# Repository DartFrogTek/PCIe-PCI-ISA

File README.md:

# Potential PCIe to PCI to ISA BUS pathway.

IT FREAKING WORKS ~~~ ISA DDMA ON WIN 10 ~~~ PCM AUDIO PLAYING ON A REAL ISA PICOGUS ON WIN10 !!!

A REAL WORLD FIRST!!! See https://www.vogons.org/viewtopic.php?t=111221 for more details.

---

This repository contains information and files on how to potentially provide modern systems with an ISA bus including ISA DMA.

More even more historical dev information that's available on the "dISAppointment - LPC to ISA adapter - ISA on modern motherboard" thread.
https://www.vogons.org/viewtopic.php?t=93291

## IT8888 based ISA8888 PCI to ISA Card
- This card/breakout board should allow a user-provided ISA Card to be translated into a PCI card via IT8888.
- ISA DMA is facilitated by PCI bus mastering through the IT8888 chip.
- Project is in KiCAD format.
- *WIP*

## ACPI SSDT 
- A way to configure motherboard bus bridges to allow I/O forwarding.
- *Boilerplate implementation*, given to me by an absolute legend.
- Added steps on how to find bridge and modify `IT8893_ACPI_SSDT.asl` for compiling.
- `IT8893_ACPI_SSDT.asl` Compiles *UNTESTED - DO NOT USE*

## DXE Driver
- Last resort, given to me by an absolute legend.
- *Boilerplate implementation*

## GRUB
- It's possible to configure PCI bridges using GRUB, avoiding the need for DXE Drivers or ACPI SSDT. 
- Requires GRUB and potentially turning off secure boot. 

## CHIPSEC
- Various LPC DMA tests with CHIPSEC
- Scripts get placed in 'chipsec-1.13.11\chipsec\modules\common'
- Tests are ran with:
  - "python chipsec_main.py -m common.lpc_dma_check"
  - "python chipsec_main.py -m common.lpc_dma_z390_test"
  - "python chipsec_main.py -m common.lpc_dma_h81_z390_test"
- *Tests work, but might crash your system.*

## Extras
- Datasheets, Documents, Pin Mappings.

## Thanks
- Everyone at Vogons, seriously thanks.
- Absolute Legend #1, #2, and #3. [Names redacted to protect their jobs]
- My wife.

Without my wife, everyone at Vogons, and the legends, none of this would likely exist.

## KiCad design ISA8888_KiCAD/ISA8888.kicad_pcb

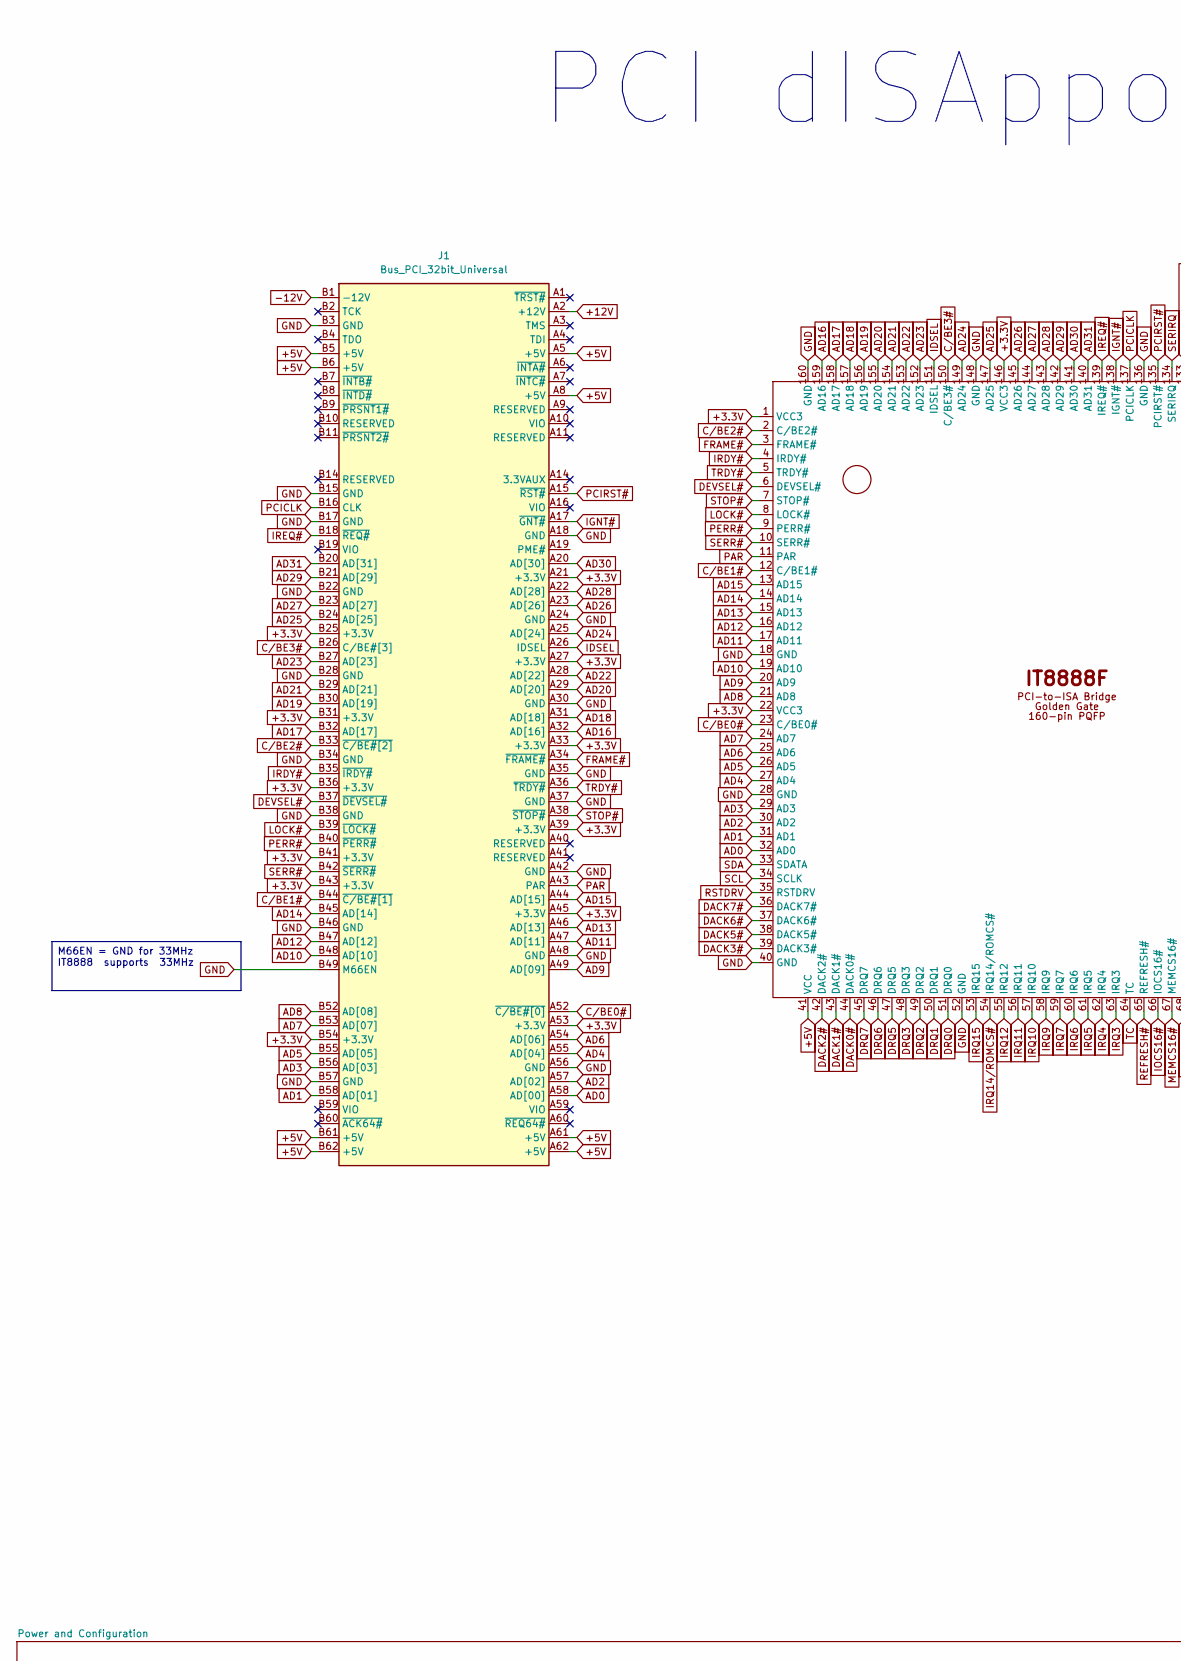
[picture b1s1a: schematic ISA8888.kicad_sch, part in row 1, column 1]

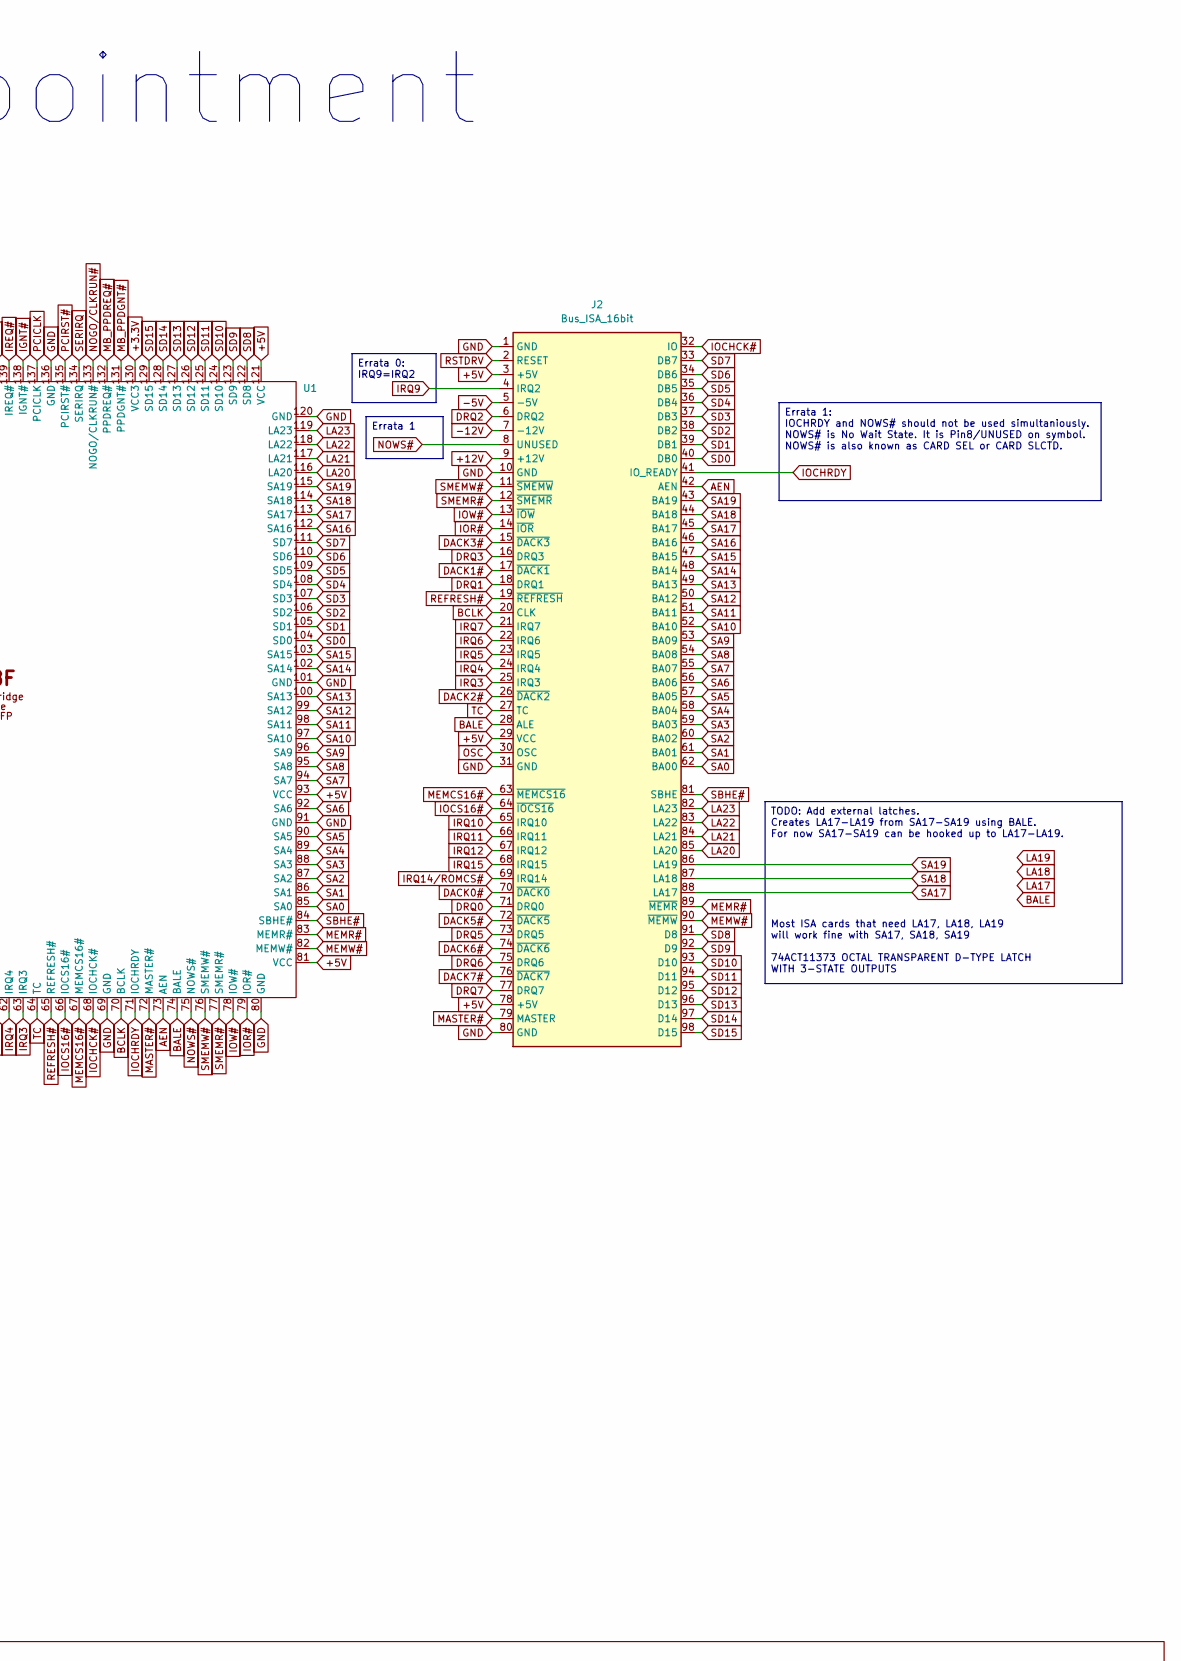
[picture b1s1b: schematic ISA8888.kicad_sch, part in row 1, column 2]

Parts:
J1: Bus_PCI_32bit_Universal; BUS_PCI
J2: Bus_ISA_16bit; CONN_EBC49_SUL_Fixed
U1: PQFP-160_28x28mm_P0.65mm

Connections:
+3.3V: J1.A21 (+3.3V), J1.A27 (+3.3V), J1.A33 (+3.3V), J1.A39 (+3.3V), J1.A45 (+3.3V), J1.A53 (+3.3V), J1.B25 (+3.3V), J1.B31 (+3.3V), J1.B36 (+3.3V), J1.B41 (+3.3V), J1.B43 (+3.3V), J1.B54 (+3.3V), U1.1 (VCC3), U1.22 (VCC3), U1.130 (VCC3), U1.146 (VCC3); also elsewhere on the board
+5V: J1.A5 (+5V), J1.A8 (+5V), J1.A61 (+5V), J1.A62 (+5V), J1.B5 (+5V), J1.B6 (+5V), J1.B61 (+5V), J1.B62 (+5V), J2.3 (+5V), J2.29 (VCC), J2.78 (+5V), U1.41 (VCC), U1.81 (VCC), U1.93 (VCC), U1.121 (VCC); also elsewhere on the board
+12V: J1.A2 (+12V), J2.9 (+12V); also elsewhere on the board
-5V: J2.5 (-5V); also elsewhere on the board
-12V: J1.B1 (-12V), J2.7 (-12V); also elsewhere on the board
AD0: J1.A58 (AD[00]), U1.32 (AD0)
AD1: J1.B58 (AD[01]), U1.31 (AD1)
AD2: J1.A57 (AD[02]), U1.30 (AD2)
AD3: J1.B56 (AD[03]), U1.29 (AD3)
AD4: J1.A55 (AD[04]), U1.27 (AD4)
AD5: J1.B55 (AD[05]), U1.26 (AD5)
AD6: J1.A54 (AD[06]), U1.25 (AD6)
AD7: J1.B53 (AD[07]), U1.24 (AD7)
AD8: J1.B52 (AD[08]), U1.21 (AD8)
AD9: J1.A49 (AD[09]), U1.20 (AD9)
AD10: J1.B48 (AD[10]), U1.19 (AD10)
AD11: J1.A47 (AD[11]), U1.17 (AD11)
AD12: J1.B47 (AD[12]), U1.16 (AD12)
AD13: J1.A46 (AD[13]), U1.15 (AD13)
AD14: J1.B45 (AD[14]), U1.14 (AD14)
AD15: J1.A44 (AD[15]), U1.13 (AD15)
AD16: J1.A32 (AD[16]), U1.159 (AD16)
AD17: J1.B32 (AD[17]), U1.158 (AD17)
AD18: J1.A31 (AD[18]), U1.157 (AD18)
AD19: J1.B30 (AD[19]), U1.156 (AD19)
AD20: J1.A29 (AD[20]), U1.155 (AD20)
AD21: J1.B29 (AD[21]), U1.154 (AD21)
AD22: J1.A28 (AD[22]), U1.153 (AD22)
AD23: J1.B27 (AD[23]), U1.152 (AD23)
AD24: J1.A25 (AD[24]), U1.149 (AD24)
AD25: J1.B24 (AD[25]), U1.147 (AD25)
AD26: J1.A23 (AD[26]), U1.145 (AD26)
AD27: J1.B23 (AD[27]), U1.144 (AD27)
AD28: J1.A22 (AD[28]), U1.143 (AD28)
AD29: J1.B21 (AD[29]), U1.142 (AD29)
AD30: J1.A20 (AD[30]), U1.141 (AD30)
AD31: J1.B20 (AD[31]), U1.140 (AD31)
AEN: J2.42 (AEN), U1.73 (AEN); also elsewhere on the board
BALE: J2.28 (ALE), U1.74 (BALE); also elsewhere on the board
BCLK: J2.20 (CLK), U1.70 (BCLK)
C/BE0#: J1.A52 (~C/BE#[0]), U1.23 (C/BE0#)
C/BE1#: J1.B44 (~C/BE#[1]), U1.12 (C/BE1#)
C/BE2#: J1.B33 (~C/BE#[2]), U1.2 (C/BE2#)
C/BE3#: J1.B26 (C/BE#[3]), U1.150 (C/BE3#)
DACK0#: J2.70 (~DACK0), U1.44 (DACK0#)
DACK1#: J2.17 (~DACK1), U1.43 (DACK1#)
DACK2#: J2.26 (~DACK2), U1.42 (DACK2#)
DACK3#: J2.15 (~DACK3), U1.39 (DACK3#)
DACK5#: J2.72 (~DACK5), U1.38 (DACK5#)
DACK6#: J2.74 (~DACK6), U1.37 (DACK6#)
DACK7#: J2.76 (~DACK7), U1.36 (DACK7#)
DEVSEL#: J1.B37 (~DEVSEL#), U1.6 (DEVSEL#)
DRQ0: J2.71 (DRQ0), U1.51 (DRQ0); also elsewhere on the board
DRQ1: J2.18 (DRQ1), U1.50 (DRQ1); also elsewhere on the board
DRQ2: J2.6 (DRQ2), U1.49 (DRQ2); also elsewhere on the board
DRQ3: J2.16 (DRQ3), U1.48 (DRQ3); also elsewhere on the board
DRQ5: J2.73 (DRQ5), U1.47 (DRQ5); also elsewhere on the board
DRQ6: J2.75 (DRQ6), U1.46 (DRQ6); also elsewhere on the board
DRQ7: J2.77 (DRQ7), U1.45 (DRQ7); also elsewhere on the board
FRAME#: J1.A34 (~FRAME#), U1.3 (FRAME#)
GND: J1.A18 (GND), J1.A24 (GND), J1.A30 (GND), J1.A35 (GND), J1.A37 (GND), J1.A42 (GND), J1.A48 (GND), J1.A56 (GND), J1.B3 (GND), J1.B15 (GND), J1.B17 (GND), J1.B22 (GND), J1.B28 (GND), J1.B34 (GND), J1.B38 (GND), J1.B46 (GND), J1.B49 (M66EN), J1.B57 (GND), J2.1 (GND), J2.10 (GND), J2.31 (GND), J2.80 (GND), U1.18 (GND), U1.28 (GND), U1.40 (GND), U1.52 (GND), U1.69 (GND), U1.80 (GND), U1.91 (GND), U1.101 (GND), U1.120 (GND), U1.136 (GND), U1.148 (GND), U1.160 (GND); also elsewhere on the board
IDSEL: J1.A26 (IDSEL), U1.151 (IDSEL)
IGNT#: J1.A17 (~GNT#), U1.138 (IGNT#); also elsewhere on the board
IOCHCK#: J2.32 (IO), U1.68 (IOCHCK#); also elsewhere on the board
IOCHRDY: J2.41 (IO_READY), U1.71 (IOCHRDY); also elsewhere on the board
IOCS16#: J2.64 (~IOCS16), U1.66 (IOCS16#); also elsewhere on the board
IOR#: J2.14 (~IOR), U1.79 (IOR#); also elsewhere on the board
IOW#: J2.13 (~IOW), U1.78 (IOW#); also elsewhere on the board
IRDY#: J1.B35 (~IRDY#), U1.4 (IRDY#)
IREQ#: J1.B18 (~REQ#), U1.139 (IREQ#); also elsewhere on the board
IRQ3: J2.25 (IRQ3), U1.63 (IRQ3)
IRQ4: J2.24 (IRQ4), U1.62 (IRQ4)
IRQ5: J2.23 (IRQ5), U1.61 (IRQ5)
IRQ6: J2.22 (IRQ6), U1.60 (IRQ6)
IRQ7: J2.21 (IRQ7), U1.59 (IRQ7)
IRQ9: J2.4 (IRQ2), U1.58 (IRQ9)
IRQ10: J2.65 (IRQ10), U1.57 (IRQ10)
IRQ11: J2.66 (IRQ11), U1.56 (IRQ11)
IRQ12: J2.67 (IRQ12), U1.55 (IRQ12)
IRQ14/ROMCS#: J2.69 (IRQ14), U1.54 (IRQ14/ROMCS#)
IRQ15: J2.68 (IRQ15), U1.53 (IRQ15)
LA20: J2.85 (LA20), U1.116 (LA20)
LA21: J2.84 (LA21), U1.117 (LA21)
LA22: J2.83 (LA22), U1.118 (LA22)
LA23: J2.82 (LA23), U1.119 (LA23)
LOCK#: J1.B39 (~LOCK#), U1.8 (LOCK#)
MASTER#: J2.79 (MASTER), U1.72 (MASTER#); also elsewhere on the board
MB_PPDGNT#: U1.131 (PPDGNT#); also elsewhere on the board
MB_PPDREQ#: U1.132 (PPDREQ#); also elsewhere on the board
MEMCS16#: J2.63 (~MEMCS16), U1.67 (MEMCS16#); also elsewhere on the board
MEMR#: J2.89 (~MEMR), U1.83 (MEMR#); also elsewhere on the board
MEMW#: J2.90 (~MEMW), U1.82 (MEMW#); also elsewhere on the board
NOGO/CLKRUN#: U1.133 (NOGO/CLKRUN#)
NOWS#: J2.8 (UNUSED), U1.75 (NOWS#); also elsewhere on the board
OSC: J2.30 (OSC); also elsewhere on the board
PAR: J1.A43 (PAR), U1.11 (PAR)
PCICLK: J1.B16 (CLK), U1.137 (PCICLK)
PCIRST#: J1.A15 (~RST#), U1.135 (PCIRST#)
PERR#: J1.B40 (~PERR#), U1.9 (PERR#)
REFRESH#: J2.19 (~REFRESH), U1.65 (REFRESH#); also elsewhere on the board
RSTDRV: J2.2 (RESET), U1.35 (RSTDRV)
SA0: J2.62 (BA00), U1.85 (SA0)
SA1: J2.61 (BA01), U1.86 (SA1)
SA2: J2.60 (BA02), U1.87 (SA2)
SA3: J2.59 (BA03), U1.88 (SA3)
SA4: J2.58 (BA04), U1.89 (SA4)
SA5: J2.57 (BA05), U1.90 (SA5)
SA6: J2.56 (BA06), U1.92 (SA6)
SA7: J2.55 (BA07), U1.94 (SA7)
SA8: J2.54 (BA08), U1.95 (SA8)
SA9: J2.53 (BA09), U1.96 (SA9)
SA10: J2.52 (BA10), U1.97 (SA10)
SA11: J2.51 (BA11), U1.98 (SA11)
SA12: J2.50 (BA12), U1.99 (SA12)
SA13: J2.49 (BA13), U1.100 (SA13)
SA14: J2.48 (BA14), U1.102 (SA14)
SA15: J2.47 (BA15), U1.103 (SA15)
SA16: J2.46 (BA16), U1.112 (SA16)
SA17: J2.45 (BA17), J2.88 (LA17), U1.113 (SA17)
SA18: J2.44 (BA18), J2.87 (LA18), U1.114 (SA18)
SA19: J2.43 (BA19), J2.86 (LA19), U1.115 (SA19)
SBHE#: J2.81 (SBHE), U1.84 (SBHE#)
SCL: U1.34 (SCLK); also elsewhere on the board
SD0: J2.40 (DB0), U1.104 (SD0); also elsewhere on the board
SD1: J2.39 (DB1), U1.105 (SD1); also elsewhere on the board
SD2: J2.38 (DB2), U1.106 (SD2); also elsewhere on the board
SD3: J2.37 (DB3), U1.107 (SD3); also elsewhere on the board
SD4: J2.36 (DB4), U1.108 (SD4); also elsewhere on the board
SD5: J2.35 (DB5), U1.109 (SD5); also elsewhere on the board
SD6: J2.34 (DB6), U1.110 (SD6); also elsewhere on the board
SD7: J2.33 (DB7), U1.111 (SD7); also elsewhere on the board
SD8: J2.91 (D8), U1.122 (SD8); also elsewhere on the board
SD9: J2.92 (D9), U1.123 (SD9); also elsewhere on the board
SD10: J2.93 (D10), U1.124 (SD10); also elsewhere on the board
SD11: J2.94 (D11), U1.125 (SD11); also elsewhere on the board
SD12: J2.95 (D12), U1.126 (SD12); also elsewhere on the board
SD13: J2.96 (D13), U1.127 (SD13); also elsewhere on the board
SD14: J2.97 (D14), U1.128 (SD14); also elsewhere on the board
SD15: J2.98 (D15), U1.129 (SD15); also elsewhere on the board
SDA: U1.33 (SDATA); also elsewhere on the board
SERIRQ: U1.134 (SERIRQ); also elsewhere on the board
SERR#: J1.B42 (~SERR#), U1.10 (SERR#)
SMEMR#: J2.12 (~SMEMR), U1.77 (SMEMR#); also elsewhere on the board
SMEMW#: J2.11 (~SMEMW), U1.76 (SMEMW#); also elsewhere on the board
STOP#: J1.A38 (~STOP#), U1.7 (STOP#)
TC: J2.27 (TC), U1.64 (TC); also elsewhere on the board
TRDY#: J1.A36 (~TRDY#), U1.5 (TRDY#)

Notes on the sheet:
PCI dISAppointment
Errata 1
Errata 0: IRQ9=IRQ2
Errata 1: IOCHRDY and NOWS# should not be used simultaniously. NOWS# is No Wait State. It is Pin8/UNUSED on symbol. NOWS# is also known as CARD SEL or CARD SLCTD.
TODO: Add external latches. Creates LA17-LA19 from SA17-SA19 using BALE. For now SA17-SA19 can be hooked up to LA17-LA19. Most ISA cards that need LA17, LA18, LA19 will work fine with SA17, SA18, SA19 74ACT11373 OCTAL TRANSPARENT D-TYPE LATCH WITH 3-STATE OUTPUTS
M66EN = GND for 33MHz IT8888 supports 33MHz

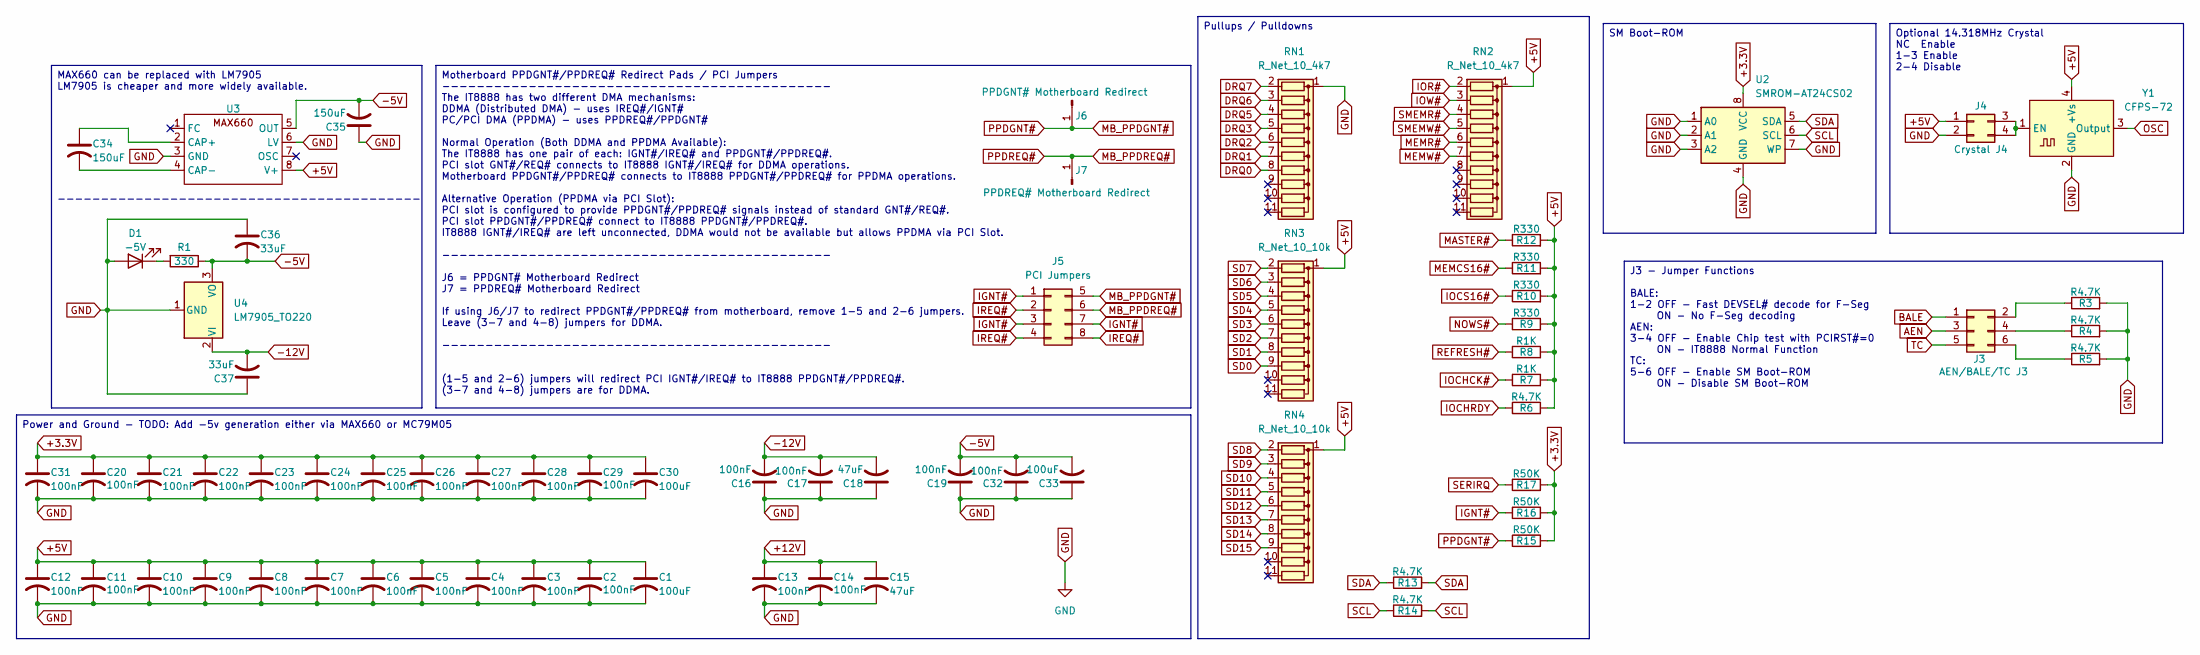
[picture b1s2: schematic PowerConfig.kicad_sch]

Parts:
C1, C30, C33: 100uF; CP_Radial_D5.0mm_P2.50mm
C2, C3, C4, C5, C6, C7, C8, C9, C10, C11, C12, C13, C14, C16, C17, C19, C20, C21, C22, C23, C24, C25, C26, C27, C28, C29, C31, C32: 100nF; C_1808_4520Metric_Pad1.72x2.30mm_HandSolder
C15, C18: 47uF; CP_Radial_D5.0mm_P2.50mm
C34, C35: 150uF; CP_Radial_D5.0mm_P2.50mm
C36, C37: 33uF; CP_Radial_D5.0mm_P2.50mm
D1: -5V; LED_D5.0mm; LCSC C99697
J3: AEN/BALE/TC J3; PinHeader_2x03_P2.00mm_Vertical
J4: Crystal J4; PinHeader_2x02_P2.00mm_Vertical
J5: PCI Jumpers; PinHeader_2x04_P2.00mm_Vertical
J6: PPDGNT# Motherboard Redirect; PinHeader_1x01_P2.00mm_Vertical
J7: PPDREQ# Motherboard Redirect; PinHeader_1x01_P2.00mm_Vertical
R1: 330; R_Axial_DIN0207_L6.3mm_D2.5mm_P7.62mm_Horizontal; LCSC C58608
R3, R4, R5, R6, R13, R14: R4.7K; R_Axial_DIN0204_L3.6mm_D1.6mm_P5.08mm_Horizontal
R7, R8: R1K; R_Axial_DIN0204_L3.6mm_D1.6mm_P5.08mm_Horizontal
R9, R10, R11, R12: R330; R_Axial_DIN0204_L3.6mm_D1.6mm_P5.08mm_Horizontal
R15, R16, R17: R50K; R_Axial_DIN0204_L3.6mm_D1.6mm_P5.08mm_Horizontal
RN1, RN2: R_Net_10_4k7; R_Array_SIP11
RN3, RN4: R_Net_10_10k; R_Array_SIP11
U2: SMROM-AT24CS02; SOIC-8_3.9x4.9mm_P1.27mm
U3: SOIC-8_3.9x4.9mm_P1.27mm
U4: LM7905_TO220; TO-220-3_Vertical
Y1: CFPS-72; Oscillator_SMD_IQD_IQXO70-4Pin_7.5x5.0mm

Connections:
+3.3V: C20.1, C21.1, C22.1, C23.1, C24.1, C25.1, C26.1, C27.1, C28.1, C29.1, C30.1, C31.1, R15.2, R16.2, R17.2, U2.8 (VCC); also elsewhere on the board
+5V: C1.1, C2.1, C3.1, C4.1, C5.1, C6.1, C7.1, C8.1, C9.1, C10.1, C11.1, C12.1, J4.1, R6.2, R7.2, R8.2, R9.2, R10.2, R11.2, R12.2, RN2.1 (common), RN3.1 (common), RN4.1 (common), U3.8 (V+), Y1.4 (+Vs); also elsewhere on the board
+12V: C13.1, C14.1, C15.1; also elsewhere on the board
-5V: C19.2, C32.2, C33.2, C35.2, C36.2, R1.1, U3.5 (OUT), U4.3 (VO); also elsewhere on the board
-12V: C16.2, C17.2, C18.2, C37.2, U4.2 (VI); also elsewhere on the board
AEN: J3.3; also elsewhere on the board
BALE: J3.1; also elsewhere on the board
DRQ0: RN1.8 (R7); also elsewhere on the board
DRQ1: RN1.7 (R6); also elsewhere on the board
DRQ2: RN1.6 (R5); also elsewhere on the board
DRQ3: RN1.5 (R4); also elsewhere on the board
DRQ5: RN1.4 (R3); also elsewhere on the board
DRQ6: RN1.3 (R2); also elsewhere on the board
DRQ7: RN1.2 (R1); also elsewhere on the board
GND: C1.2, C2.2, C3.2, C4.2, C5.2, C6.2, C7.2, C8.2, C9.2, C10.2, C11.2, C12.2, C13.2, C14.2, C15.2, C16.1, C17.1, C18.1, C19.1, C20.2, C21.2, C22.2, C23.2, C24.2, C25.2, C26.2, C27.2, C28.2, C29.2, C30.2, C31.2, C32.1, C33.1, C35.1, C36.1, C37.1, D1.2 (A), J4.2, R3.2, R4.2, R5.2, RN1.1 (common), U2.1 (A0), U2.2 (A1), U2.3 (A2), U2.4 (GND), U2.7 (WP), U3.3 (GND), U3.6 (LV), U4.1 (GND), Y1.2 (GND); also elsewhere on the board
IGNT#: J5.1, J5.3, J5.7, R16.1; also elsewhere on the board
IOCHCK#: R7.1; also elsewhere on the board
IOCHRDY: R6.1; also elsewhere on the board
IOCS16#: R10.1; also elsewhere on the board
IOR#: RN2.2 (R1); also elsewhere on the board
IOW#: RN2.3 (R2); also elsewhere on the board
IREQ#: J5.2, J5.4, J5.8; also elsewhere on the board
MASTER#: R12.1; also elsewhere on the board
MB_PPDGNT#: J5.5, J6.1, R15.1; also elsewhere on the board
MB_PPDREQ#: J5.6, J7.1; also elsewhere on the board
MEMCS16#: R11.1; also elsewhere on the board
MEMR#: RN2.6 (R5); also elsewhere on the board
MEMW#: RN2.7 (R6); also elsewhere on the board
NOWS#: R9.1; also elsewhere on the board
unnamed: D1.1 (K), R1.2
unnamed: J3.2, R3.1
unnamed: J3.4, R4.1
unnamed: J3.6, R5.1
unnamed: J4.3, J4.4, Y1.1 (EN)
unnamed: C34.1, U3.2 (CAP+)
unnamed: C34.2, U3.4 (CAP-)
OSC: Y1.3 (Output); also elsewhere on the board
REFRESH#: R8.1; also elsewhere on the board
SCL: R14.1, R14.2, U2.6 (SCL); also elsewhere on the board
SD0: RN3.9 (R8); also elsewhere on the board
SD1: RN3.8 (R7); also elsewhere on the board
SD2: RN3.7 (R6); also elsewhere on the board
SD3: RN3.6 (R5); also elsewhere on the board
SD4: RN3.5 (R4); also elsewhere on the board
SD5: RN3.4 (R3); also elsewhere on the board
SD6: RN3.3 (R2); also elsewhere on the board
SD7: RN3.2 (R1); also elsewhere on the board
SD8: RN4.2 (R1); also elsewhere on the board
SD9: RN4.3 (R2); also elsewhere on the board
SD10: RN4.4 (R3); also elsewhere on the board
SD11: RN4.5 (R4); also elsewhere on the board
SD12: RN4.6 (R5); also elsewhere on the board
SD13: RN4.7 (R6); also elsewhere on the board
SD14: RN4.8 (R7); also elsewhere on the board
SD15: RN4.9 (R8); also elsewhere on the board
SDA: R13.1, R13.2, U2.5 (SDA); also elsewhere on the board
SERIRQ: R17.1; also elsewhere on the board
SMEMR#: RN2.4 (R3); also elsewhere on the board
SMEMW#: RN2.5 (R4); also elsewhere on the board
TC: J3.5; also elsewhere on the board

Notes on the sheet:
MAX660 can be replaced with LM7905 LM7905 is cheaper and more widely available. ------------------------------------------
Motherboard PPDGNT#/PPDREQ# Redirect Pads / PCI Jumpers --------------------------------------------- The IT8888 has two different DMA mechanisms: DDMA (Distributed DMA) - uses IREQ#/IGNT# PC/PCI DMA (PPDMA) - uses PPDREQ#/PPDGNT# Normal Operation (Both DDMA and PPDMA Available): The IT8888 has one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
Pullups / Pulldowns
SM Boot-ROM
J3 - Jumper Functions BALE: 1-2 OFF - Fast DEVSEL# decode for F-Seg ON - No F-Seg decoding AEN: 3-4 OFF - Enable Chip test with PCIRST#=0 ON - IT8888 Normal Function TC: 5-6 OFF - Enable SM Boot-ROM ON - Disable SM Boot-ROM
Power and Ground - TODO: Add -5v generation either via MAX660 or MC79M05
Optional 14.318MHz Crystal NC Enable 1-3 Enable 2-4 Disable

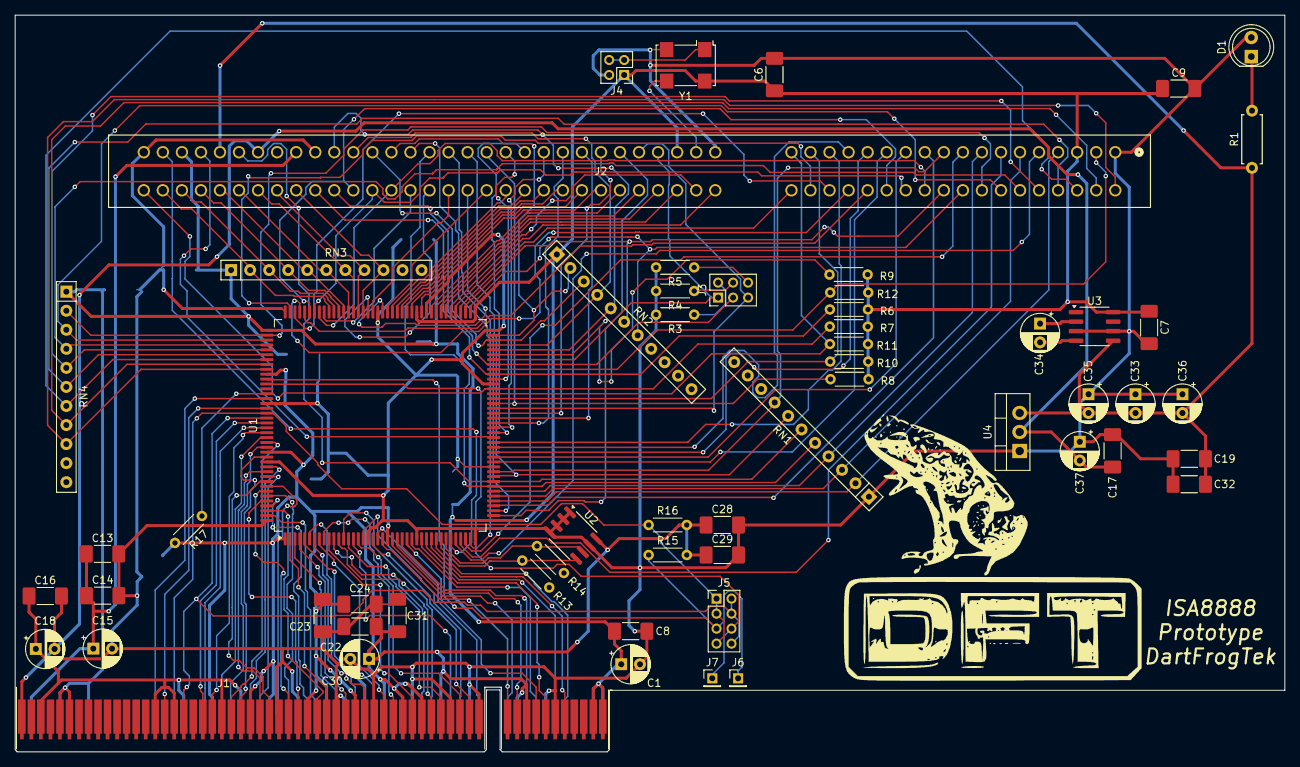
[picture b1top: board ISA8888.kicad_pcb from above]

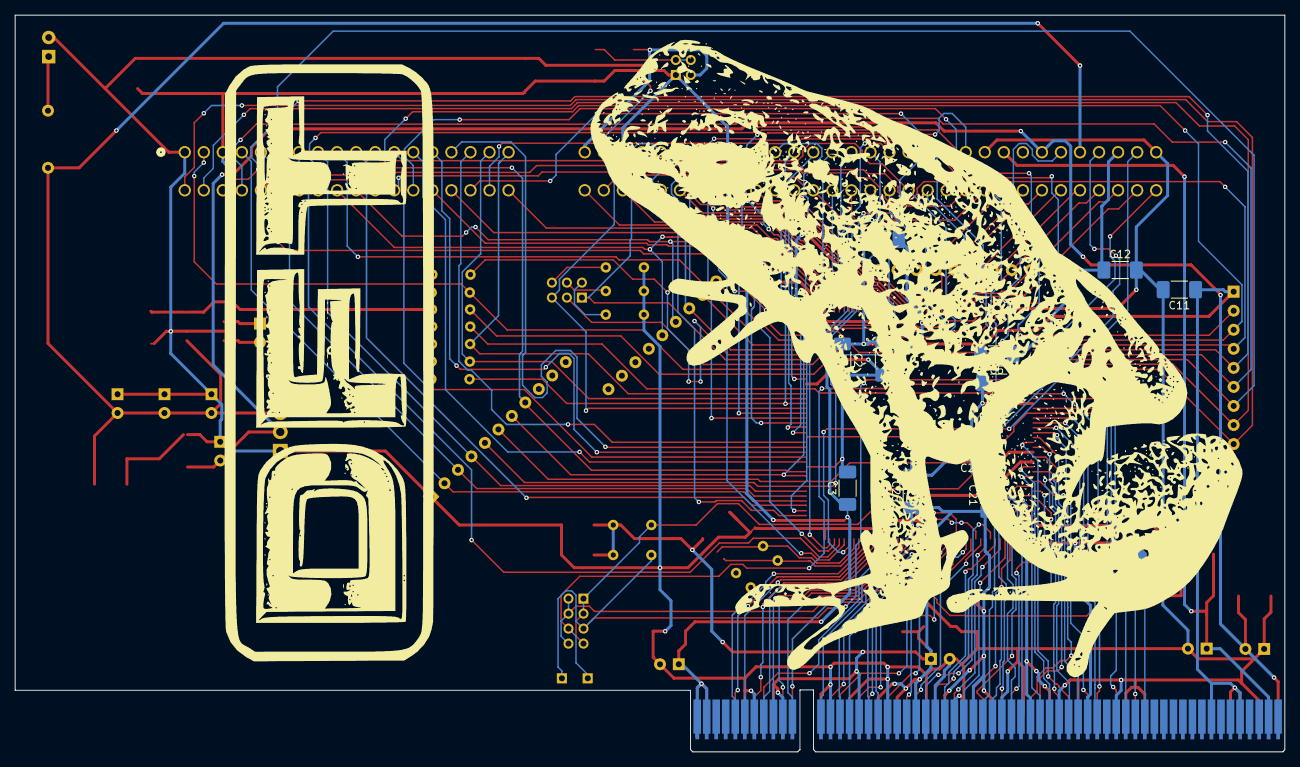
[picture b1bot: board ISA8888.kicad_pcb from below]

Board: 2 copper layers, 169.3 x 98.2 mm, 70 parts (12 on the bottom side), 153 nets.

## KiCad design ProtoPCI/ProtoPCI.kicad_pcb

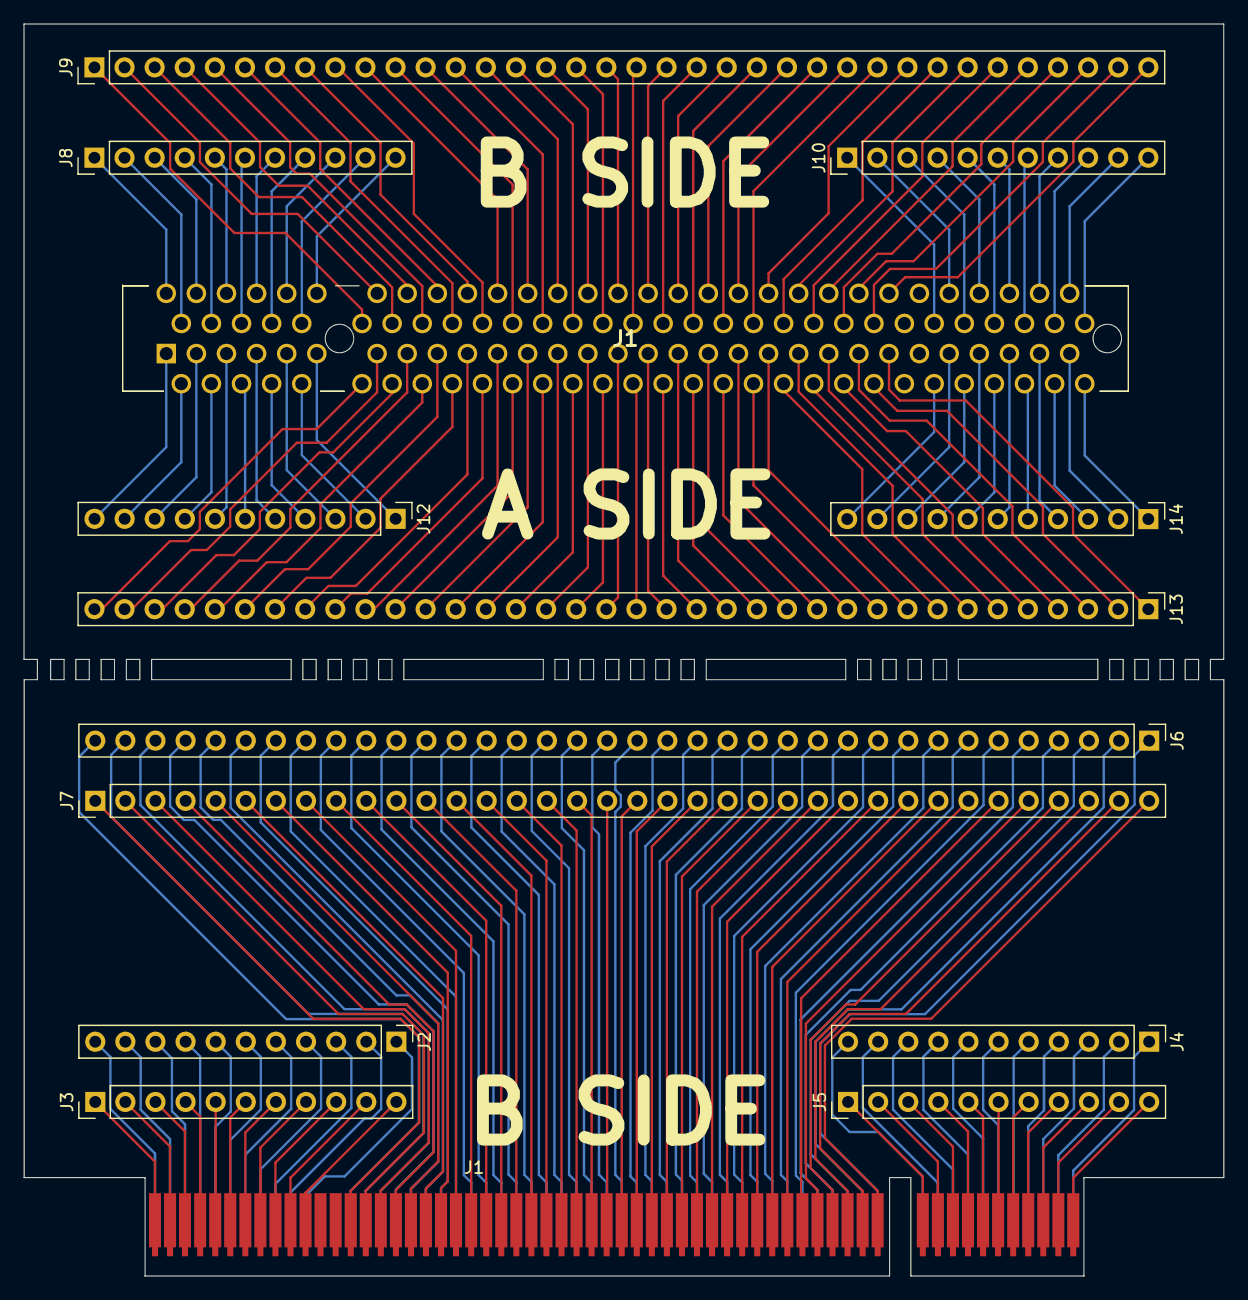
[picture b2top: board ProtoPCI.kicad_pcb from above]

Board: 2 copper layers, 101.2 x 105.6 mm, 14 parts (0 on the bottom side), 116 nets.

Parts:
J1: Bus_PCI_32bit_Universal; BUS_PCI
J1#2: Bus_PCI_32bit_Universal_Slot; 51451541
J2, J3, J4, J5, J8, J10, J12, J14: Conn_01x11_Pin; PinHeader_1x11_P2.54mm_Vertical
J6, J7, J9, J13: Conn_01x36_Pin; PinHeader_1x36_P2.54mm_Vertical

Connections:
unnamed: J1.A14 (3.3VAUX), J1#2.A14 (3.3VAUX), J6.36, J13.36
unnamed: J1.A2 (+12V), J1#2.A2 (+12V), J2.10, J12.10
unnamed: J1.B1 (-12V), J1#2.B1 (-12V), J3.1, J8.1
unnamed: J1.A58 (AD[00]), J1#2.A58 (AD[00]), J4.5, J14.5
unnamed: J1.B58 (AD[01]), J1#2.B58 (AD[01]), J5.7, J10.7
unnamed: J1.A57 (AD[02]), J1#2.A57 (AD[02]), J4.6, J14.6
unnamed: J1.B56 (AD[03]), J1#2.B56 (AD[03]), J5.5, J10.5
unnamed: J1.A55 (AD[04]), J1#2.A55 (AD[04]), J4.8, J14.8
unnamed: J1.B55 (AD[05]), J1#2.B55 (AD[05]), J5.4, J10.4
unnamed: J1.A54 (AD[06]), J1#2.A54 (AD[06]), J4.9, J14.9
unnamed: J1.B53 (AD[07]), J1#2.B53 (AD[07]), J5.2, J10.2
unnamed: J1.B52 (AD[08]), J1#2.B52 (AD[08]), J5.1, J10.1
unnamed: J1.A49 (AD[09]), J1#2.A49 (AD[09]), J6.1, J13.1
unnamed: J1.B48 (AD[10]), J1#2.B48 (AD[10]), J7.35, J9.35
unnamed: J1.A47 (AD[11]), J1#2.A47 (AD[11]), J6.3, J13.3
unnamed: J1.B47 (AD[12]), J1#2.B47 (AD[12]), J7.34, J9.34
unnamed: J1.A46 (AD[13]), J1#2.A46 (AD[13]), J6.4, J13.4
unnamed: J1.B45 (AD[14]), J1#2.B45 (AD[14]), J7.32, J9.32
unnamed: J1.A44 (AD[15]), J1#2.A44 (AD[15]), J6.6, J13.6
unnamed: J1.A32 (AD[16]), J1#2.A32 (AD[16]), J6.18, J13.18
unnamed: J1.B32 (AD[17]), J1#2.B32 (AD[17]), J7.19, J9.19
unnamed: J1.A31 (AD[18]), J1#2.A31 (AD[18]), J6.19, J13.19
unnamed: J1.B30 (AD[19]), J1#2.B30 (AD[19]), J7.17, J9.17
unnamed: J1.A29 (AD[20]), J1#2.A29 (AD[20]), J6.21, J13.21
unnamed: J1.B29 (AD[21]), J1#2.B29 (AD[21]), J7.16, J9.16
unnamed: J1.A28 (AD[22]), J1#2.A28 (AD[22]), J6.22, J13.22
unnamed: J1.B27 (AD[23]), J1#2.B27 (AD[23]), J7.14, J9.14
unnamed: J1.A25 (AD[24]), J1#2.A25 (AD[24]), J6.25, J13.25
unnamed: J1.B24 (AD[25]), J1#2.B24 (AD[25]), J7.11, J9.11
unnamed: J1.A23 (AD[26]), J1#2.A23 (AD[26]), J6.27, J13.27
unnamed: J1.B23 (AD[27]), J1#2.B23 (AD[27]), J7.10, J9.10
unnamed: J1.A22 (AD[28]), J1#2.A22 (AD[28]), J6.28, J13.28
unnamed: J1.B21 (AD[29]), J1#2.B21 (AD[29]), J7.8, J9.8
unnamed: J1.A20 (AD[30]), J1#2.A20 (AD[30]), J6.30, J13.30
unnamed: J1.B20 (AD[31]), J1#2.B20 (AD[31]), J7.7, J9.7
unnamed: J1.B16 (CLK), J1#2.B16 (CLK), J7.3, J9.3
unnamed: J1.B26 (C/BE#[3]), J1#2.B26 (C/BE#[3]), J7.13, J9.13
unnamed: J1.A26 (IDSEL), J1#2.A26 (IDSEL), J6.24, J13.24
unnamed: J1.B49 (M66EN), J1#2.B49 (M66EN), J7.36, J9.36
unnamed: J1.A43 (PAR), J1#2.A43 (PAR), J6.7, J13.7
unnamed: J1.A19 (PME#), J1#2.A19 (PME#), J6.31, J13.31
unnamed: J1.B2 (TCK), J1#2.B2 (TCK), J3.2, J8.2
unnamed: J1.A4 (TDI), J1#2.A4 (TDI), J2.8, J12.8
unnamed: J1.B4 (TDO), J1#2.B4 (TDO), J3.4, J8.4
unnamed: J1.A3 (TMS), J1#2.A3 (TMS), J2.9, J12.9
unnamed: J1.B60 (~ACK64#), J1#2.B60 (~ACK64#), J5.9, J10.9
unnamed: J1.A52 (~C/BE#[0]), J1#2.A52 (~C/BE#[0]), J4.11, J14.11
unnamed: J1.B44 (~C/BE#[1]), J1#2.B44 (~C/BE#[1]), J7.31, J9.31
unnamed: J1.B33 (~C/BE#[2]), J1#2.B33 (~C/BE#[2]), J7.20, J9.20
unnamed: J1.B37 (~DEVSEL#), J1#2.B37 (~DEVSEL#), J7.24, J9.24
unnamed: J1.A34 (~FRAME#), J1#2.A34 (~FRAME#), J6.16, J13.16
unnamed: J1.A17 (~GNT#), J1#2.A17 (~GNT#), J6.33, J13.33
unnamed: J1.A6 (~INTA#), J1#2.A6 (~INTA#), J2.6, J12.6
unnamed: J1.B7 (~INTB#), J1#2.B7 (~INTB#), J3.7, J8.7
unnamed: J1.A7 (~INTC#), J1#2.A7 (~INTC#), J2.5, J12.5
unnamed: J1.B8 (~INTD#), J1#2.B8 (~INTD#), J3.8, J8.8
unnamed: J1.B35 (~IRDY#), J1#2.B35 (~IRDY#), J7.22, J9.22
unnamed: J1.B39 (~LOCK#), J1#2.B39 (~LOCK#), J7.26, J9.26
unnamed: J1.B40 (~PERR#), J1#2.B40 (~PERR#), J7.27, J9.27
unnamed: J1.B9 (~PRSNT1#), J1#2.B9 (~PRSNT1#), J3.9, J8.9
unnamed: J1.B11 (~PRSNT2#), J1#2.B11 (~PRSNT2#), J3.11, J8.11
unnamed: J1.A60 (~REQ64#), J1#2.A60 (~REQ64#), J4.3, J14.3
unnamed: J1.B18 (~REQ#), J1#2.B18 (~REQ#), J7.5, J9.5
unnamed: J1.A15 (~RST#), J1#2.A15 (~RST#), J6.35, J13.35
unnamed: J1.B42 (~SERR#), J1#2.B42 (~SERR#), J7.29, J9.29
unnamed: J1.A38 (~STOP#), J1#2.A38 (~STOP#), J6.12, J13.12
unnamed: J1.A36 (~TRDY#), J1#2.A36 (~TRDY#), J6.14, J13.14
unnamed: J1.A1 (~TRST#), J1#2.A1 (~TRST#), J2.11, J12.11
unnamed: J1.A11 (RESERVED), J1#2.A11 (RESERVED), J2.1, J12.1
unnamed: J1.A10 (VIO), J1#2.A10 (VIO), J2.2, J12.2
unnamed: J1.A9 (RESERVED), J1#2.A9 (RESERVED), J2.3, J12.3
unnamed: J1.A8 (+5V), J1#2.A8 (+5V), J2.4, J12.4
unnamed: J1.A5 (+5V), J1#2.A5 (+5V), J2.7, J12.7
unnamed: J1.B3 (GND), J1#2.B3 (GND), J3.3, J8.3
unnamed: J1.B5 (+5V), J1#2.B5 (+5V), J3.5, J8.5
unnamed: J1.B6 (+5V), J1#2.B6 (+5V), J3.6, J8.6
unnamed: J1.B10 (RESERVED), J1#2.B10 (RESERVED), J3.10, J8.10
unnamed: J1.A62 (+5V), J1#2.A62 (+5V), J4.1, J14.1
unnamed: J1.A61 (+5V), J1#2.A61 (+5V), J4.2, J14.2
unnamed: J1.A59 (VIO), J1#2.A59 (VIO), J4.4, J14.4
unnamed: J1.A56 (GND), J1#2.A56 (GND), J4.7, J14.7
unnamed: J1.A53 (+3.3V), J1#2.A53 (+3.3V), J4.10, J14.10
unnamed: J1.B54 (+3.3V), J1#2.B54 (+3.3V), J5.3, J10.3
unnamed: J1.B57 (GND), J1#2.B57 (GND), J5.6, J10.6
unnamed: J1.B59 (VIO), J1#2.B59 (VIO), J5.8, J10.8
unnamed: J1.B61 (+5V), J1#2.B61 (+5V), J5.10, J10.10
unnamed: J1.B62 (+5V), J1#2.B62 (+5V), J5.11, J10.11
unnamed: J1.A48 (GND), J1#2.A48 (GND), J6.2, J13.2
unnamed: J1.A45 (+3.3V), J1#2.A45 (+3.3V), J6.5, J13.5
unnamed: J1.A42 (GND), J1#2.A42 (GND), J6.8, J13.8
unnamed: J1.A41 (RESERVED), J1#2.A41 (RESERVED), J6.9, J13.9
unnamed: J1.A40 (RESERVED), J1#2.A40 (RESERVED), J6.10, J13.10
unnamed: J1.A39 (+3.3V), J1#2.A39 (+3.3V), J6.11, J13.11
unnamed: J1.A37 (GND), J1#2.A37 (GND), J6.13, J13.13
unnamed: J1.A35 (GND), J1#2.A35 (GND), J6.15, J13.15
unnamed: J1.A33 (+3.3V), J1#2.A33 (+3.3V), J6.17, J13.17
unnamed: J1.A30 (GND), J1#2.A30 (GND), J6.20, J13.20
unnamed: J1.A27 (+3.3V), J1#2.A27 (+3.3V), J6.23, J13.23
unnamed: J1.A24 (GND), J1#2.A24 (GND), J6.26, J13.26
unnamed: J1.A21 (+3.3V), J1#2.A21 (+3.3V), J6.29, J13.29
unnamed: J1.A18 (GND), J1#2.A18 (GND), J6.32, J13.32
unnamed: J1.A16 (VIO), J1#2.A16 (VIO), J6.34, J13.34
unnamed: J1.B14 (RESERVED), J1#2.B14 (RESERVED), J7.1, J9.1
unnamed: J1.B15 (GND), J1#2.B15 (GND), J7.2, J9.2
unnamed: J1.B17 (GND), J1#2.B17 (GND), J7.4, J9.4
unnamed: J1.B19 (VIO), J1#2.B19 (VIO), J7.6, J9.6
unnamed: J1.B22 (GND), J1#2.B22 (GND), J7.9, J9.9
unnamed: J1.B25 (+3.3V), J1#2.B25 (+3.3V), J7.12, J9.12
unnamed: J1.B28 (GND), J1#2.B28 (GND), J7.15, J9.15
unnamed: J1.B31 (+3.3V), J1#2.B31 (+3.3V), J7.18, J9.18
unnamed: J1.B34 (GND), J1#2.B34 (GND), J7.21, J9.21
unnamed: J1.B36 (+3.3V), J1#2.B36 (+3.3V), J7.23, J9.23
unnamed: J1.B38 (GND), J1#2.B38 (GND), J7.25, J9.25
unnamed: J1.B41 (+3.3V), J1#2.B41 (+3.3V), J7.28, J9.28
unnamed: J1.B43 (+3.3V), J1#2.B43 (+3.3V), J7.30, J9.30
unnamed: J1.B46 (GND), J1#2.B46 (GND), J7.33, J9.33
